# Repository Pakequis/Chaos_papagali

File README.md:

# **Chaos Papagali**

A slightly over-engineered, annoying device that imitates the vibration of a phone.

## About the project:

This project is an update of the classic electronic cricket circuit that we saw in old electronics magazines. It's a prank device aimed at annoying someone (especially my daughters and my wife). Today, there are devices like the [OpenKobold](https://github.com/Seitanas/OpenKobold) and the [Annoyng PCB](https://annoyingpcb.com/) that play random sounds, but none imitate the vibration of a phone. So, I created one that does.

Chaos Papagali is a little bigger (50 x 21 mm) than Annoyng PCB (44 x 24 mm):

In addition to being annoying with its random vibrations, the Chaos Papagali also has the function of only operating in the dark for maximum inconvenience.

## Demo video:

## Hardware:

The circuit is a mashup of an Arduino and a battery charger from [OSHWLab](https://oshwlab.com/Little_Arc/TP4056).

The boards were developed in kicad 8.0. There are two PCBs in one panel, one for the circuit and another for support the battery and motor. It is necessary to break the PCB in half during final assembly. The two boards are stacked and secured with double sided tape over the battery.

The project had three phases:

1. Proof of concept assembled with an RGBDuino and a prototyping shield.
2. Prototype using an Arduino Pro Mini and a battery charger module.
3. Final circuit on a two-PCB stack.

The device is powered by a 400 mAh battery and operates with a current consumption of approximately 500 µA in low power mode. This configuration ensures several days of use between charges, depending on the operating interval and the type of motor employed.

The ATMEGA328 microcontroller runs well at 16MHz on battery, although it would be better to lower the frequency using an 8MHz crystal.

## Firmware:
There are two sketches (.ino), one with the main program and another with the functions. 

The firmware goes into low power mode and triggers the vibration motor at random intervals. 

The dip switch selection options:

Dip 1 and 2: Mode of vibration:
    00 = Phone call.
    01 = Phone alarm.
    10 = Phone notification.
    11 = Chaos mode (all modes above, at random).

Dip 3: Day or night function. With 0 the device works with light on the LDR. With 1 the device works only in the dark.

Dip 4: Time short or long. 0 = short time (1 to 10 minutes). 1 = Long time (10 to 60 minutes interval).

## Notes:
1. At first, I considered adding a buzzer to mimic the end-of-cycle sound found in some home appliances. I was able to replicate the beeps of my microwave, but I couldn't manage to imitate those of the washing machine. It seems that washing machine manufacturers opted for a more complex buzzer circuit for some reason.

In these machines, they implement a circuit with frequency and envelope outputs to play classical music (such as "Die Forelle," for example). Since it was taking a long time to develop this part, I decided to remove the buzzer from the project.

2. In some cases, it is necessary to secure the PCB to the surface with adhesive tape or by placing a weight on it; otherwise, it may 'walk' on the surface.

3. Image of a parrot (Papagali in Romanian) generated with AI, because I don't have the gift for drawing. The project name is a reference to that [song](https://www.youtube.com/watch?v=nYc09Xqy3hE) by the second greatest metal band in the world.

4. Is possible to make this with a couple of LM555? Maybe...

## Contact:
Feel free to reach out to me on social media: @pakequis in any of them...

You can also send me an email at pakequis (at Gmail).

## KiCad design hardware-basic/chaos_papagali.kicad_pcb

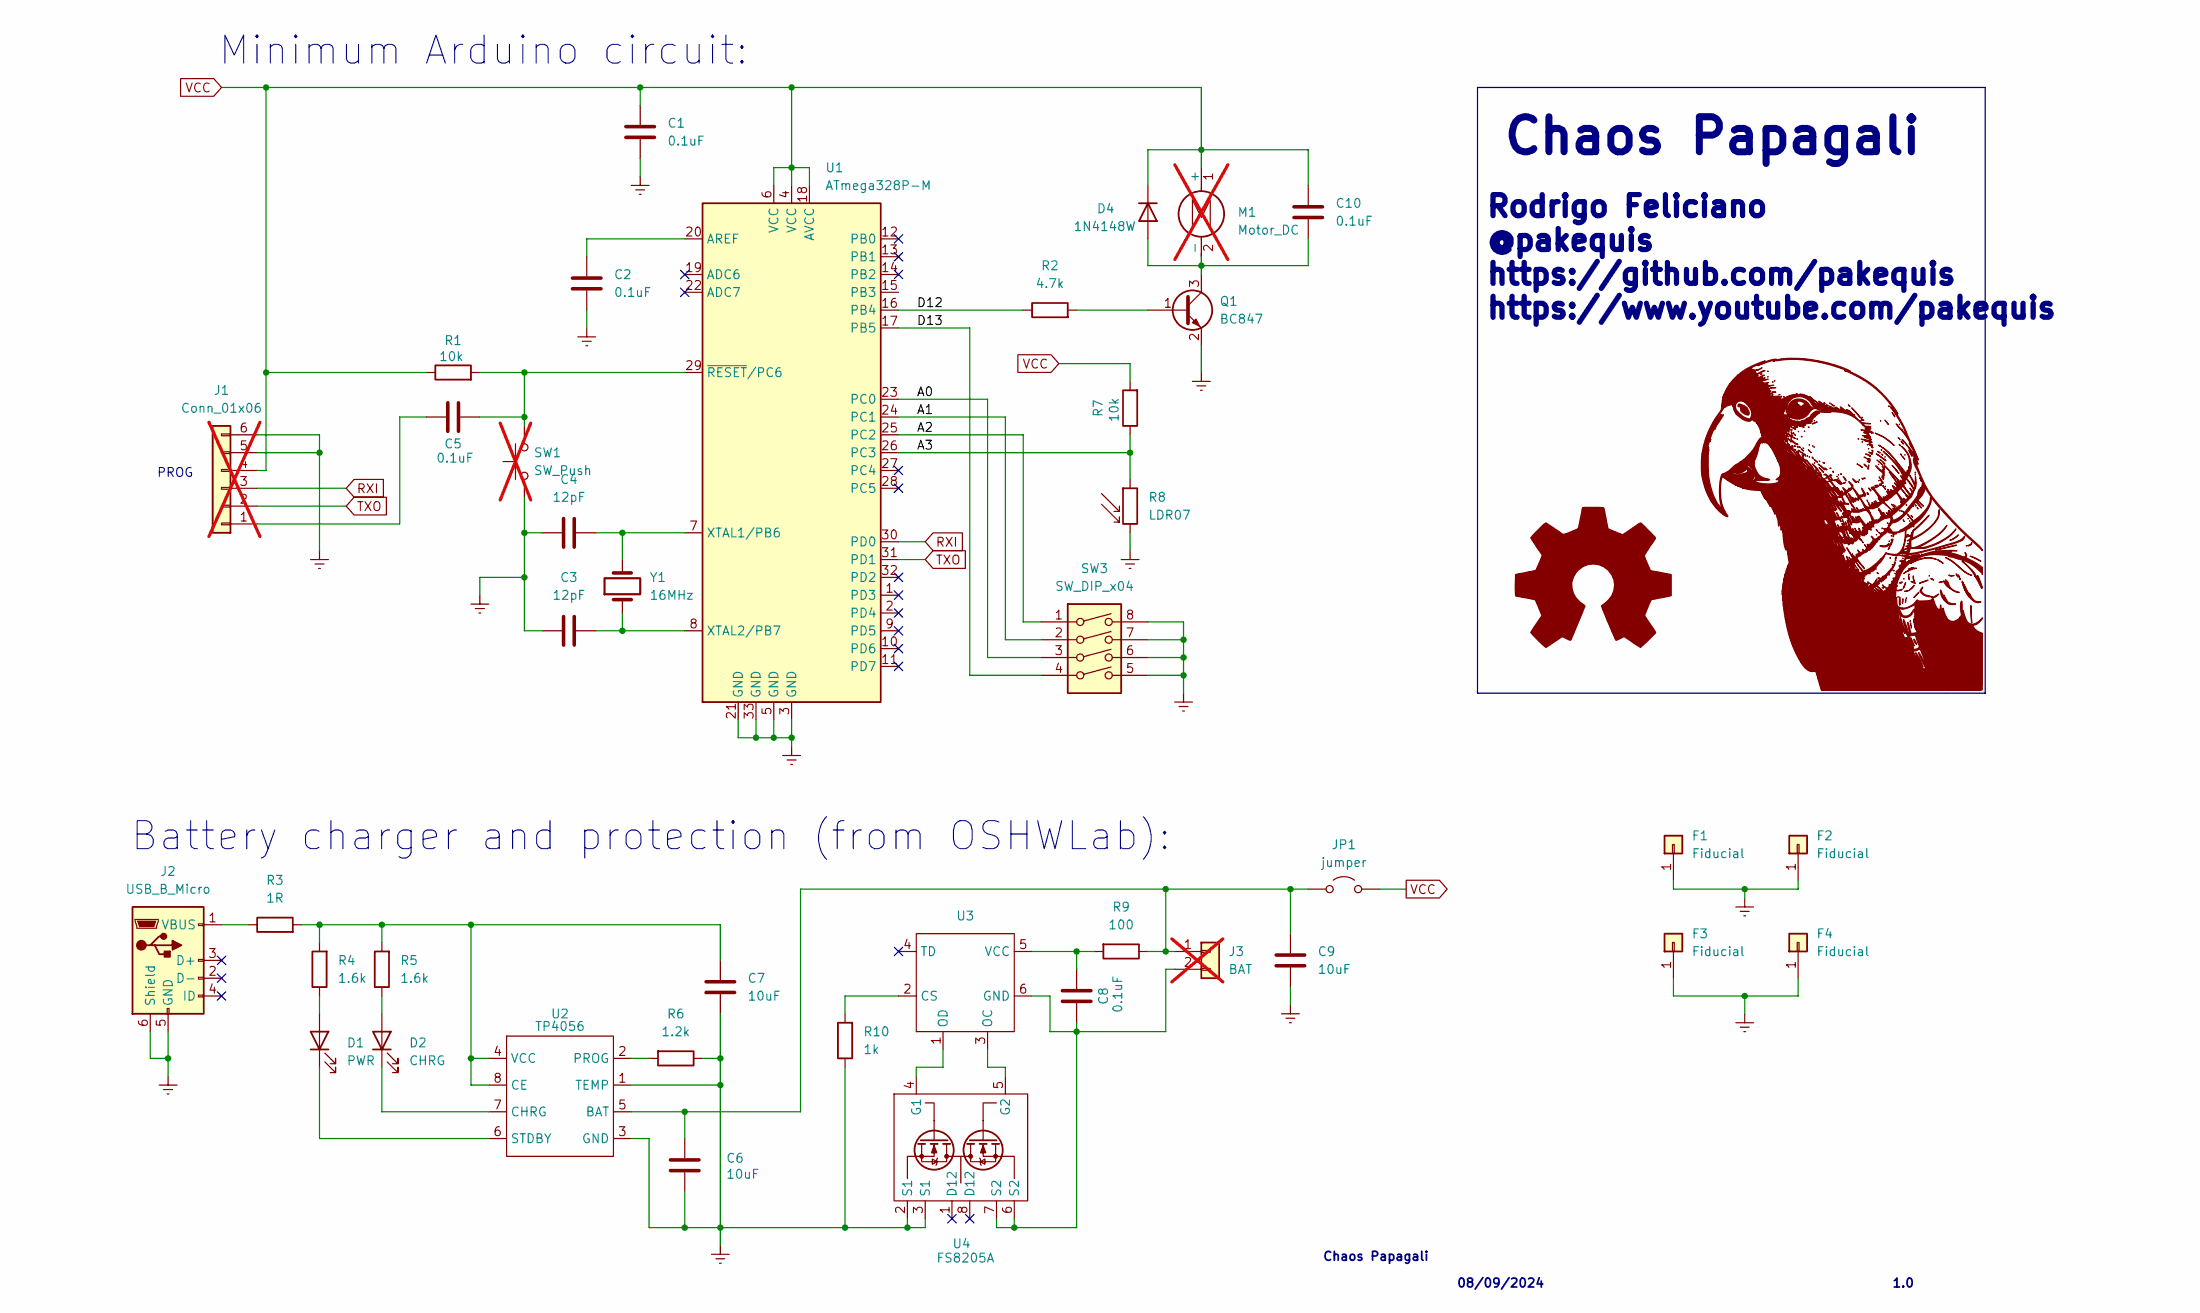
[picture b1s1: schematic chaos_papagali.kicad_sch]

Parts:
C1, C2, C5, C8, C10: 0.1uF; C_0603_1608Metric_Pad1.08x0.95mm_HandSolder
C3, C4: 12pF; C_0603_1608Metric_Pad1.08x0.95mm_HandSolder
C6, C7, C9: 10uF; C_0603_1608Metric_Pad1.08x0.95mm_HandSolder
D1: PWR; LED_0603_1608Metric_Pad1.05x0.95mm_HandSolder
D2: CHRG; LED_0603_1608Metric_Pad1.05x0.95mm_HandSolder
D4: 1N4148W; D_SOD-123
F1, F2, F3, F4: Fiducial; Fiducial_0.5mm_Mask1.5mm
J1: Conn_01x06; PinHeader_1x06_P2.54mm_Vertical; not fitted
J2: USB_B_Micro; USB_Micro-B_Amphenol_10103594-0001LF_Horizontal
J3: BAT; PinHeader_1x02_P2.54mm_Vertical; not fitted
JP1: jumper; PinHeader_1x02_P2.54mm_Vertical
M1: Motor_DC; PinHeader_1x02_P2.54mm_Vertical; not fitted
Q1: BC847; SOT-23
R1, R7: 10k; R_0603_1608Metric_Pad0.98x0.95mm_HandSolder
R2: 4.7k; R_0603_1608Metric_Pad0.98x0.95mm_HandSolder
R3: 1R; R_0603_1608Metric_Pad0.98x0.95mm_HandSolder
R4, R5: 1.6k; R_0603_1608Metric_Pad0.98x0.95mm_HandSolder
R6: 1.2k; R_0603_1608Metric_Pad0.98x0.95mm_HandSolder
R8: LDR07; R_LDR_5.1x4.3mm_P3.4mm_Vertical
R9: 100; R_0603_1608Metric_Pad0.98x0.95mm_HandSolder
R10: 1k; R_0603_1608Metric_Pad0.98x0.95mm_HandSolder
SW1: SW_Push; PinHeader_1x02_P2.54mm_Vertical; not fitted
SW3: SW_DIP_x04; SW_DIP_SPSTx04_Slide_9.78x12.34mm_W7.62mm_P2.54mm
U1: ATmega328P-M; QFN-32-1EP_5x5mm_P0.5mm_EP3.1x3.1mm
U2: TP4056; SOP-8_3.9x4.9mm_P1.27mm
U3: SOT-23-6
U4: FS8205A; TSSOP-8_4.4x3mm_P0.65mm
Y1: 16MHz; Crystal_HC49-U_Vertical

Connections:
/A3: R7.1, R8.1, U1.26 (PC3)
/D5: SW3.2, U1.24 (PC1)
/D6: SW3.3, U1.23 (PC0)
/D7: SW3.4, U1.17 (PB5)
/D12: R2.1, U1.16 (PB4)
GNDREF: C1.2, C2.2, C3.1, C4.1, C6.1, C7.1, C9.1, F1.1, F2.1, F3.1, F4.1, J1.5, J1.6, J2.5 (GND), J2.6 (Shield), Q1.2 (E), R6.1, R8.2, R10.1, SW1.1, SW3.5, SW3.6, SW3.7, SW3.8, U1.3 (GND), U1.5 (GND), U1.21 (GND), U1.33 (GND), U2.1 (TEMP), U2.3 (GND), U4.2 (S1), U4.3 (S1)
unnamed: D1.2 (A), R4.1
unnamed: D1.1 (K), U2.6 (STDBY)
unnamed: D2.2 (A), R5.1
unnamed: D2.1 (K), U2.7 (CHRG)
unnamed: C10.2, D4.2 (A), M1.2 (-), Q1.3 (C)
unnamed: C5.1, J1.1
unnamed: J2.1 (VBUS), R3.1
unnamed: C6.2, C9.2, J3.1, JP1.1 (A), R9.1, U2.5 (BAT)
unnamed: C8.1, J3.2, U3.6 (GND), U4.6 (S2), U4.7 (S2)
unnamed: Q1.1 (B), R2.2
unnamed: C2.1, U1.20 (AREF)
unnamed: SW3.1, U1.25 (PC2)
unnamed: C4.2, U1.7 (XTAL1/PB6), Y1.2
unnamed: C3.2, U1.8 (XTAL2/PB7), Y1.1
unnamed: C5.2, R1.2, SW1.2, U1.29 (~RESET/PC6)
unnamed: C7.2, R3.2, R4.2, R5.2, U2.4 (VCC), U2.8 (CE)
unnamed: R6.2, U2.2 (PROG)
unnamed: R10.2, U3.2 (CS)
unnamed: U3.3 (OC), U4.5 (G2)
unnamed: U3.1 (OD), U4.4 (G1)
unnamed: C8.2, R9.2, U3.5 (VCC)
RXI: J1.3, U1.30 (PD0)
TXO: J1.2, U1.31 (PD1)
VCC: C1.1, C10.1, D4.1 (K), J1.4, JP1.2 (B), M1.1 (+), R1.1, R7.2, U1.4 (VCC), U1.6 (VCC), U1.18 (AVCC)

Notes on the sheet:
Chaos Papagali
Battery charger and protection (from OSHWLab):
Minimum Arduino circuit:
08/09/2024
Rodrigo Feliciano @pakequis https://github.com/pakequis https://www.youtube.com/pakequis
PROG
1.0

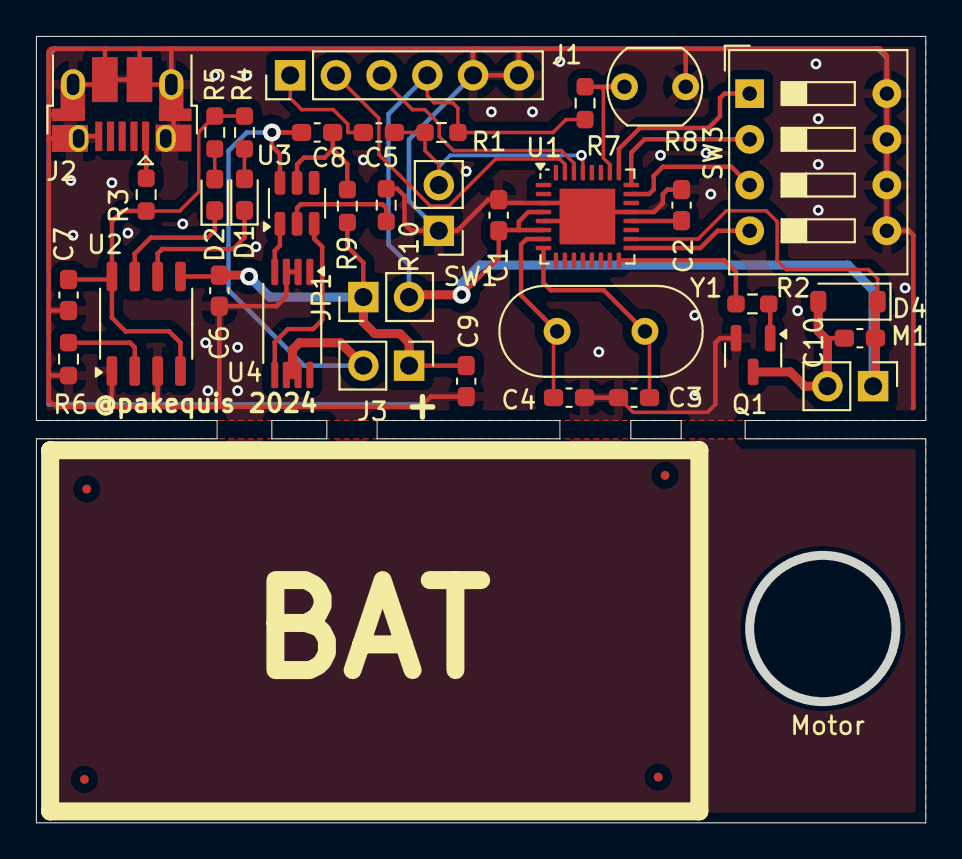
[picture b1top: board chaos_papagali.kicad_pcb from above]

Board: 2 copper layers, 49.0 x 43.2 mm, 40 parts (0 on the bottom side), 30 nets.

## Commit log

2024-09-14 First full project commit
2024-09-14 Readme.md adjust
2024-09-14 Firmware folder
2024-09-14 Add note...
